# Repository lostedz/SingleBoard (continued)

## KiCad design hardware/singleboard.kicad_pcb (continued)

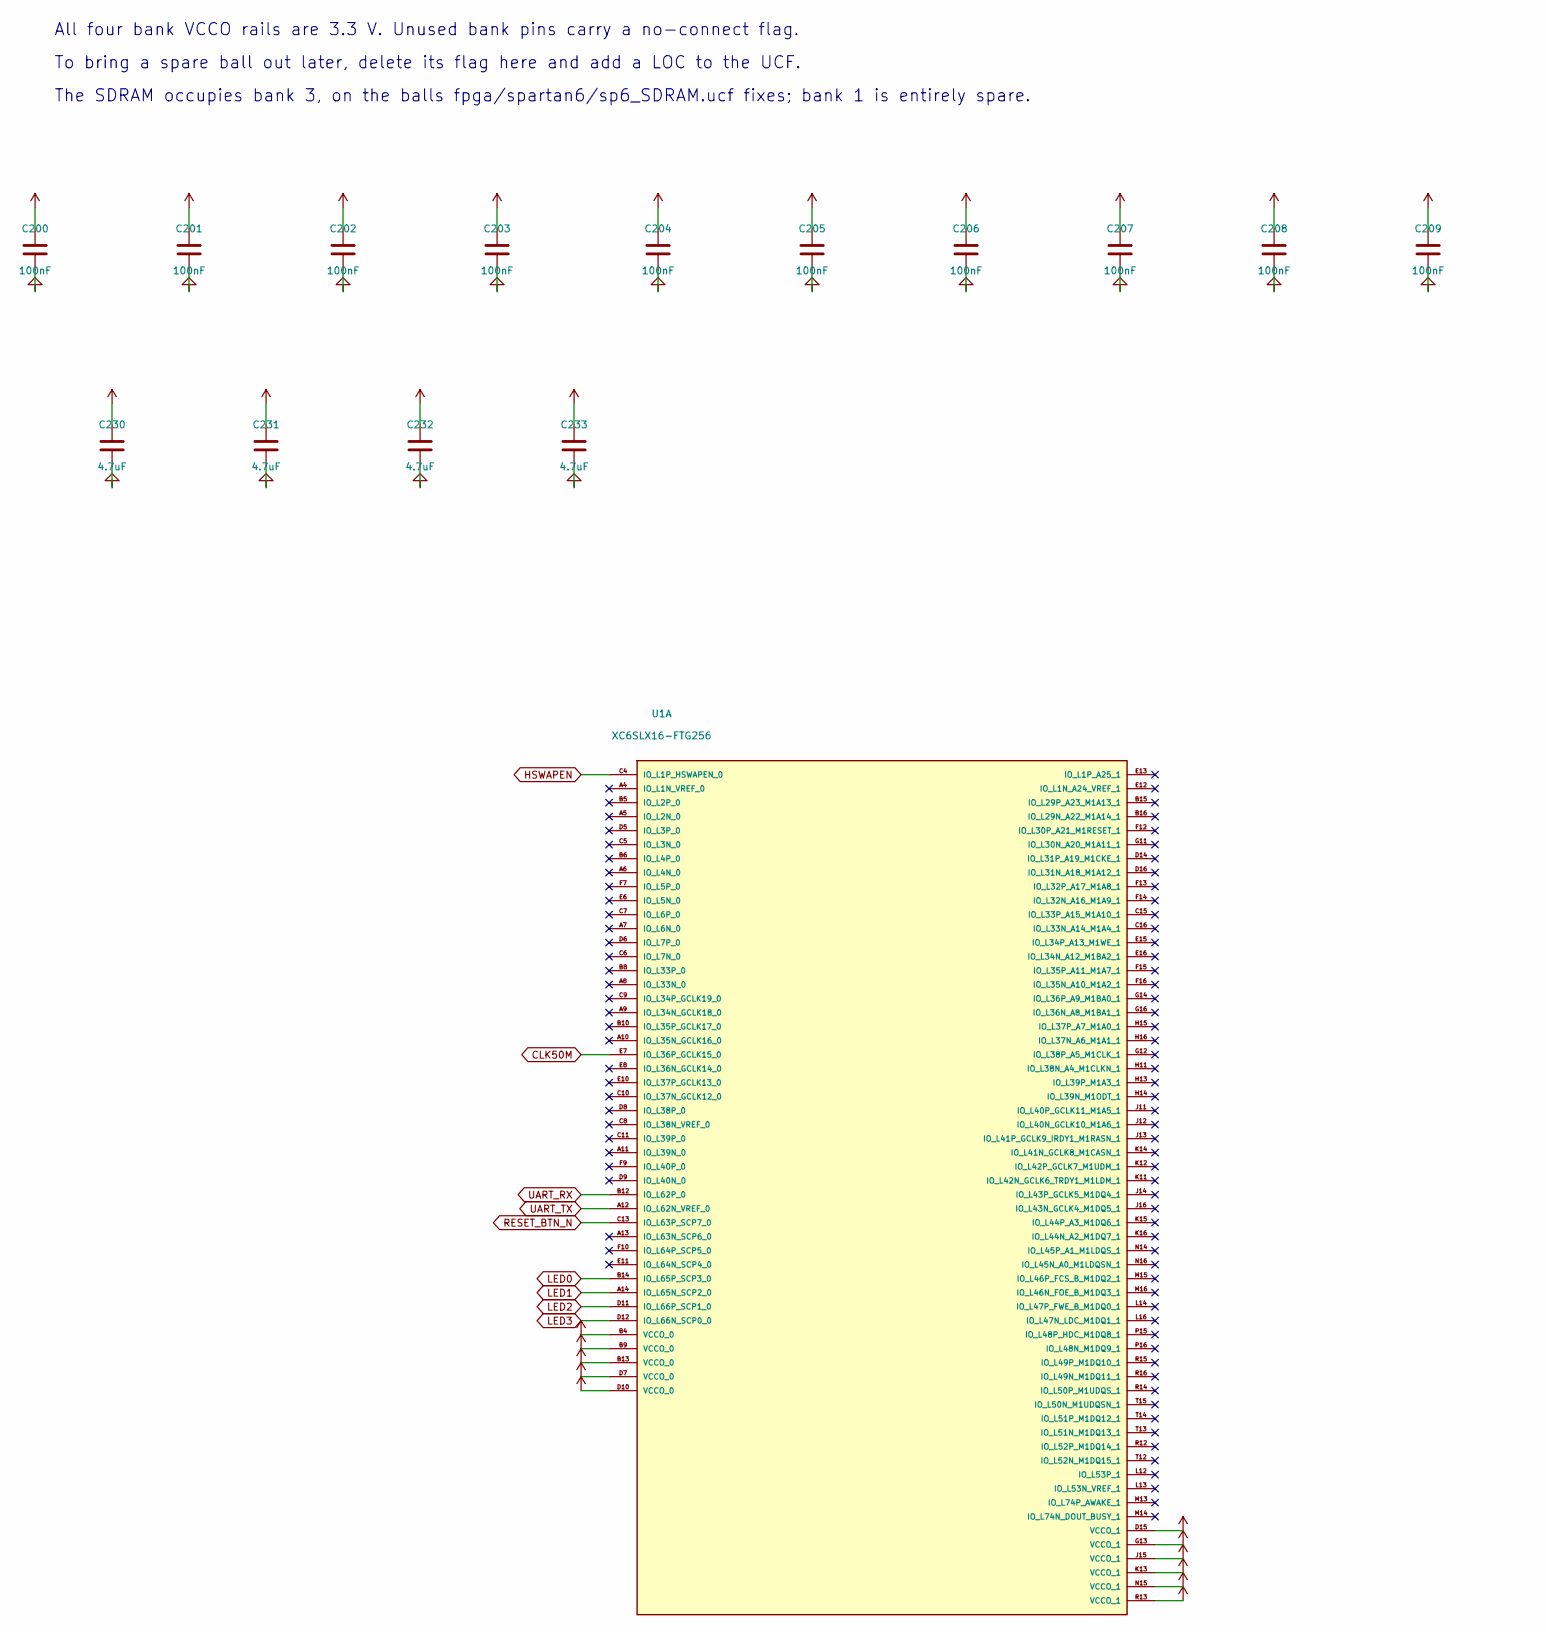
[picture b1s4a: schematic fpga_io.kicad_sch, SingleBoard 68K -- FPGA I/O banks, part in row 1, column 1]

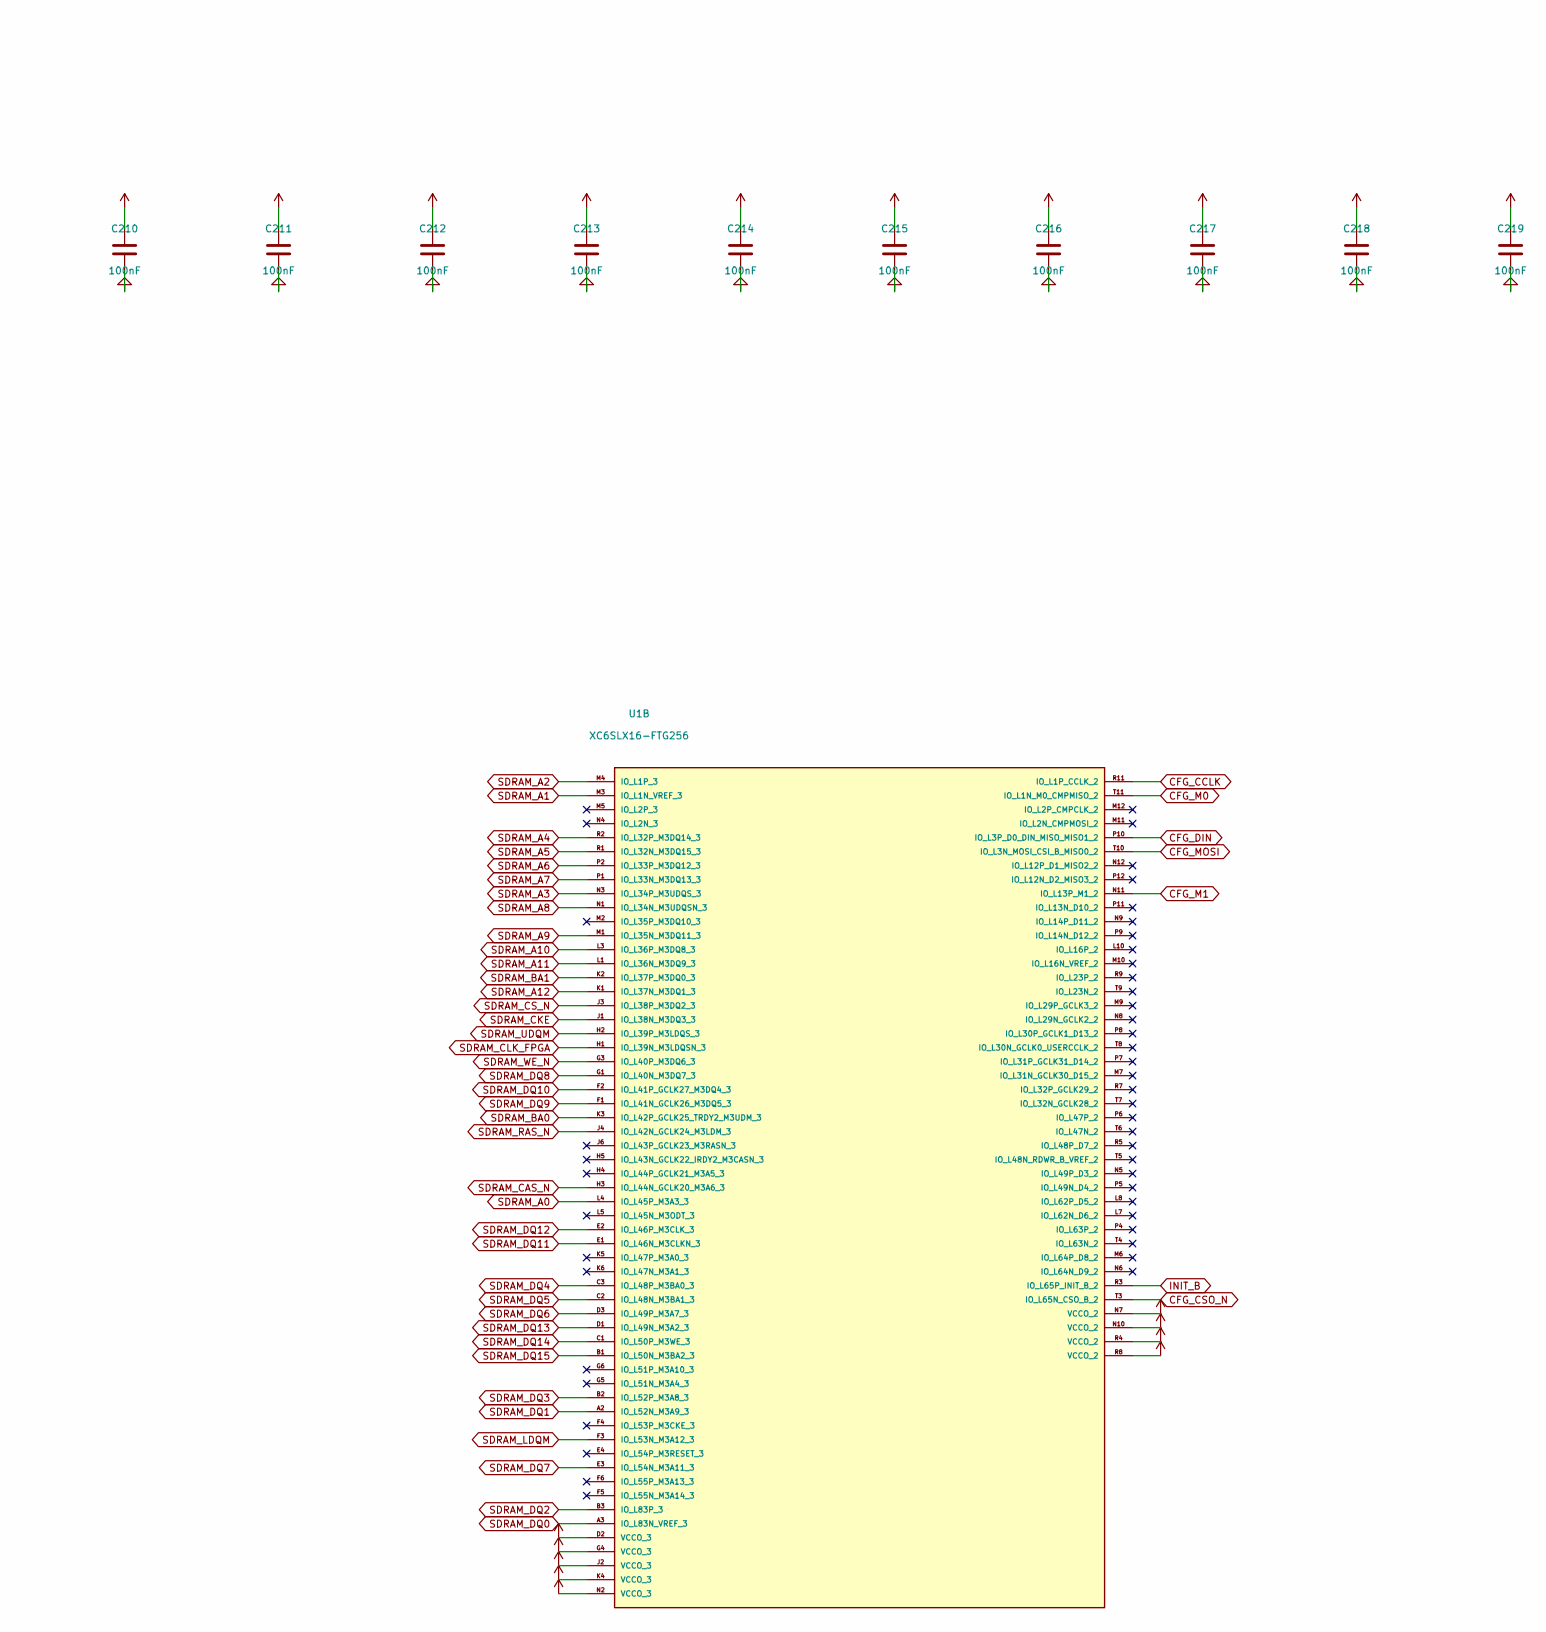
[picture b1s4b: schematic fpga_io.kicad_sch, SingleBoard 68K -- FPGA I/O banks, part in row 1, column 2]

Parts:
C200, C201, C202, C203, C204, C205, C206, C207, C208, C209, C210, C211, C212, C213, C214, C215, C216, C217, C218, C219: 100nF; C_0402_1005Metric
C230, C231, C232, C233: 4.7uF; C_0805_2012Metric
U1: XC6SLX16-FTG256; Xilinx_FTG256

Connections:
+3V3: C200.1, C201.1, C202.1, C203.1, C204.1, C205.1, C206.1, C207.1, C208.1, C209.1, C210.1, C211.1, C212.1, C213.1, C214.1, C215.1, C216.1, C217.1, C218.1, C219.1, C230.1, C231.1, C232.1, C233.1, U1.B4 (VCCO_0), U1.B9 (VCCO_0), U1.B13 (VCCO_0), U1.D2 (VCCO_3), U1.D7 (VCCO_0), U1.D10 (VCCO_0), U1.D15 (VCCO_1), U1.G4 (VCCO_3), U1.G13 (VCCO_1), U1.J2 (VCCO_3), U1.J15 (VCCO_1), U1.K4 (VCCO_3), U1.K13 (VCCO_1), U1.N2 (VCCO_3), U1.N7 (VCCO_2), U1.N10 (VCCO_2), U1.N15 (VCCO_1), U1.R4 (VCCO_2), U1.R8 (VCCO_2), U1.R13 (VCCO_1); also elsewhere on the board
CFG_CCLK: U1.R11 (IO_L1P_CCLK_2); also elsewhere on the board
CFG_CSO_N: U1.T3 (IO_L65N_CSO_B_2); also elsewhere on the board
CFG_DIN: U1.P10 (IO_L3P_D0_DIN_MISO_MISO1_2); also elsewhere on the board
CFG_M0: U1.T11 (IO_L1N_M0_CMPMISO_2); also elsewhere on the board
CFG_M1: U1.N11 (IO_L13P_M1_2); also elsewhere on the board
CFG_MOSI: U1.T10 (IO_L3N_MOSI_CSI_B_MISO0_2); also elsewhere on the board
CLK50M: U1.E7 (IO_L36P_GCLK15_0); also elsewhere on the board
GND: C200.2, C201.2, C202.2, C203.2, C204.2, C205.2, C206.2, C207.2, C208.2, C209.2, C210.2, C211.2, C212.2, C213.2, C214.2, C215.2, C216.2, C217.2, C218.2, C219.2, C230.2, C231.2, C232.2, C233.2; also elsewhere on the board
HSWAPEN: U1.C4 (IO_L1P_HSWAPEN_0); also elsewhere on the board
INIT_B: U1.R3 (IO_L65P_INIT_B_2); also elsewhere on the board
LED0: U1.B14 (IO_L65P_SCP3_0); also elsewhere on the board
LED1: U1.A14 (IO_L65N_SCP2_0); also elsewhere on the board
LED2: U1.D11 (IO_L66P_SCP1_0); also elsewhere on the board
LED3: U1.D12 (IO_L66N_SCP0_0); also elsewhere on the board
RESET_BTN_N: U1.C13 (IO_L63P_SCP7_0); also elsewhere on the board
SDRAM_A0: U1.L4 (IO_L45P_M3A3_3); also elsewhere on the board
SDRAM_A1: U1.M3 (IO_L1N_VREF_3); also elsewhere on the board
SDRAM_A2: U1.M4 (IO_L1P_3); also elsewhere on the board
SDRAM_A3: U1.N3 (IO_L34P_M3UDQS_3); also elsewhere on the board
SDRAM_A4: U1.R2 (IO_L32P_M3DQ14_3); also elsewhere on the board
SDRAM_A5: U1.R1 (IO_L32N_M3DQ15_3); also elsewhere on the board
SDRAM_A6: U1.P2 (IO_L33P_M3DQ12_3); also elsewhere on the board
SDRAM_A7: U1.P1 (IO_L33N_M3DQ13_3); also elsewhere on the board
SDRAM_A8: U1.N1 (IO_L34N_M3UDQSN_3); also elsewhere on the board
SDRAM_A9: U1.M1 (IO_L35N_M3DQ11_3); also elsewhere on the board
SDRAM_A10: U1.L3 (IO_L36P_M3DQ8_3); also elsewhere on the board
SDRAM_A11: U1.L1 (IO_L36N_M3DQ9_3); also elsewhere on the board
SDRAM_A12: U1.K1 (IO_L37N_M3DQ1_3); also elsewhere on the board
SDRAM_BA0: U1.K3 (IO_L42P_GCLK25_TRDY2_M3UDM_3); also elsewhere on the board
SDRAM_BA1: U1.K2 (IO_L37P_M3DQ0_3); also elsewhere on the board
SDRAM_CAS_N: U1.H3 (IO_L44N_GCLK20_M3A6_3); also elsewhere on the board
SDRAM_CKE: U1.J1 (IO_L38N_M3DQ3_3); also elsewhere on the board
SDRAM_CLK_FPGA: U1.H1 (IO_L39N_M3LDQSN_3); also elsewhere on the board
SDRAM_CS_N: U1.J3 (IO_L38P_M3DQ2_3); also elsewhere on the board
SDRAM_DQ0: U1.A3 (IO_L83N_VREF_3); also elsewhere on the board
SDRAM_DQ1: U1.A2 (IO_L52N_M3A9_3); also elsewhere on the board
SDRAM_DQ2: U1.B3 (IO_L83P_3); also elsewhere on the board
SDRAM_DQ3: U1.B2 (IO_L52P_M3A8_3); also elsewhere on the board
SDRAM_DQ4: U1.C3 (IO_L48P_M3BA0_3); also elsewhere on the board
SDRAM_DQ5: U1.C2 (IO_L48N_M3BA1_3); also elsewhere on the board
SDRAM_DQ6: U1.D3 (IO_L49P_M3A7_3); also elsewhere on the board
SDRAM_DQ7: U1.E3 (IO_L54N_M3A11_3); also elsewhere on the board
SDRAM_DQ8: U1.G1 (IO_L40N_M3DQ7_3); also elsewhere on the board
SDRAM_DQ9: U1.F1 (IO_L41N_GCLK26_M3DQ5_3); also elsewhere on the board
SDRAM_DQ10: U1.F2 (IO_L41P_GCLK27_M3DQ4_3); also elsewhere on the board
SDRAM_DQ11: U1.E1 (IO_L46N_M3CLKN_3); also elsewhere on the board
SDRAM_DQ12: U1.E2 (IO_L46P_M3CLK_3); also elsewhere on the board
SDRAM_DQ13: U1.D1 (IO_L49N_M3A2_3); also elsewhere on the board
SDRAM_DQ14: U1.C1 (IO_L50P_M3WE_3); also elsewhere on the board
SDRAM_DQ15: U1.B1 (IO_L50N_M3BA2_3); also elsewhere on the board
SDRAM_LDQM: U1.F3 (IO_L53N_M3A12_3); also elsewhere on the board
SDRAM_RAS_N: U1.J4 (IO_L42N_GCLK24_M3LDM_3); also elsewhere on the board
SDRAM_UDQM: U1.H2 (IO_L39P_M3LDQS_3); also elsewhere on the board
SDRAM_WE_N: U1.G3 (IO_L40P_M3DQ6_3); also elsewhere on the board
UART_RX: U1.B12 (IO_L62P_0); also elsewhere on the board
UART_TX: U1.A12 (IO_L62N_VREF_0); also elsewhere on the board

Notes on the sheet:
All four bank VCCO rails are 3.3 V. Unused bank pins carry a no-connect flag.
To bring a spare ball out later, delete its flag here and add a LOC to the UCF.
The SDRAM occupies bank 3, on the balls fpga/spartan6/sp6_SDRAM.ucf fixes; bank 1 is entirely spare.

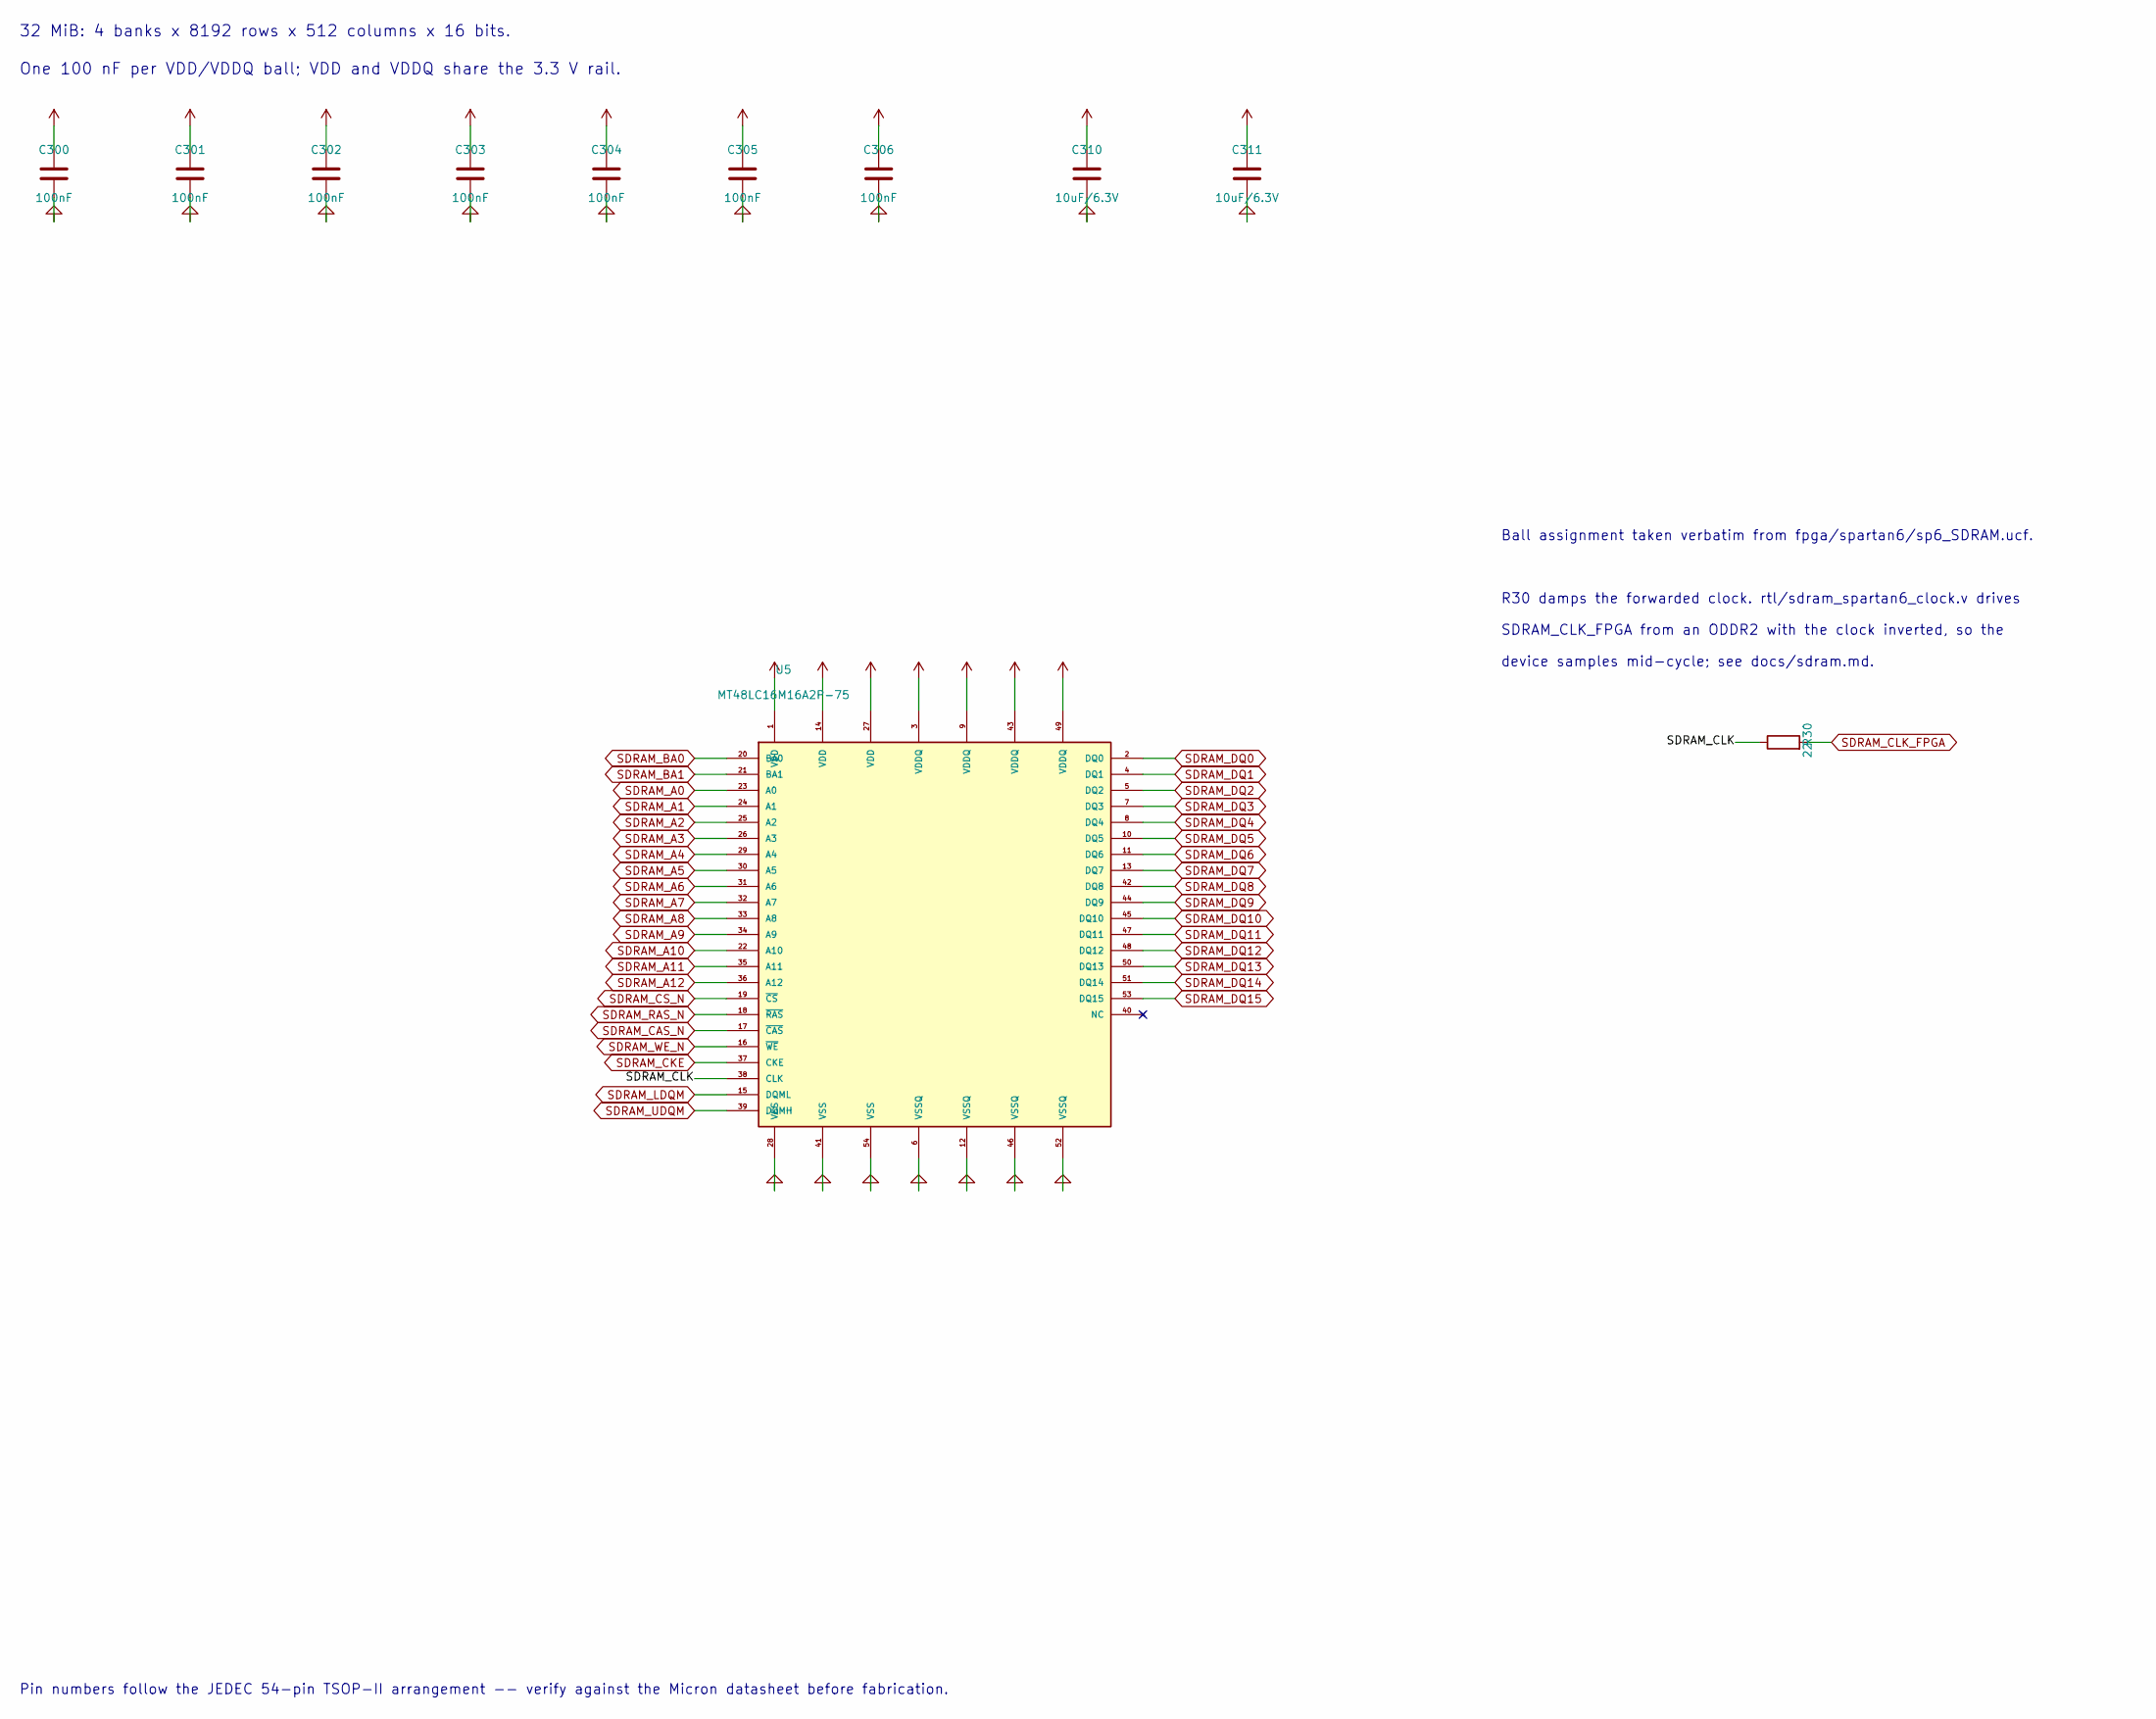
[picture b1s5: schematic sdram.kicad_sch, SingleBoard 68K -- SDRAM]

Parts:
C300, C301, C302, C303, C304, C305, C306: 100nF; C_0402_1005Metric
C310, C311: 10uF/6.3V; C_0805_2012Metric
R30: 22; R_0402_1005Metric
U5: MT48LC16M16A2P-75; TSOP-II-54_22.2x10.16mm_P0.8mm

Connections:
+3V3: C300.1, C301.1, C302.1, C303.1, C304.1, C305.1, C306.1, C310.1, C311.1, U5.1 (VDD), U5.3 (VDDQ), U5.9 (VDDQ), U5.14 (VDD), U5.27 (VDD), U5.43 (VDDQ), U5.49 (VDDQ); also elsewhere on the board
/sdram/SDRAM_CLK: R30.1, U5.38 (CLK)
GND: C300.2, C301.2, C302.2, C303.2, C304.2, C305.2, C306.2, C310.2, C311.2, U5.6 (VSSQ), U5.12 (VSSQ), U5.28 (VSS), U5.41 (VSS), U5.46 (VSSQ), U5.52 (VSSQ), U5.54 (VSS); also elsewhere on the board
SDRAM_A0: U5.23 (A0); also elsewhere on the board
SDRAM_A1: U5.24 (A1); also elsewhere on the board
SDRAM_A2: U5.25 (A2); also elsewhere on the board
SDRAM_A3: U5.26 (A3); also elsewhere on the board
SDRAM_A4: U5.29 (A4); also elsewhere on the board
SDRAM_A5: U5.30 (A5); also elsewhere on the board
SDRAM_A6: U5.31 (A6); also elsewhere on the board
SDRAM_A7: U5.32 (A7); also elsewhere on the board
SDRAM_A8: U5.33 (A8); also elsewhere on the board
SDRAM_A9: U5.34 (A9); also elsewhere on the board
SDRAM_A10: U5.22 (A10); also elsewhere on the board
SDRAM_A11: U5.35 (A11); also elsewhere on the board
SDRAM_A12: U5.36 (A12); also elsewhere on the board
SDRAM_BA0: U5.20 (BA0); also elsewhere on the board
SDRAM_BA1: U5.21 (BA1); also elsewhere on the board
SDRAM_CAS_N: U5.17 (~CAS); also elsewhere on the board
SDRAM_CKE: U5.37 (CKE); also elsewhere on the board
SDRAM_CLK_FPGA: R30.2; also elsewhere on the board
SDRAM_CS_N: U5.19 (~CS); also elsewhere on the board
SDRAM_DQ0: U5.2 (DQ0); also elsewhere on the board
SDRAM_DQ1: U5.4 (DQ1); also elsewhere on the board
SDRAM_DQ2: U5.5 (DQ2); also elsewhere on the board
SDRAM_DQ3: U5.7 (DQ3); also elsewhere on the board
SDRAM_DQ4: U5.8 (DQ4); also elsewhere on the board
SDRAM_DQ5: U5.10 (DQ5); also elsewhere on the board
SDRAM_DQ6: U5.11 (DQ6); also elsewhere on the board
SDRAM_DQ7: U5.13 (DQ7); also elsewhere on the board
SDRAM_DQ8: U5.42 (DQ8); also elsewhere on the board
SDRAM_DQ9: U5.44 (DQ9); also elsewhere on the board
SDRAM_DQ10: U5.45 (DQ10); also elsewhere on the board
SDRAM_DQ11: U5.47 (DQ11); also elsewhere on the board
SDRAM_DQ12: U5.48 (DQ12); also elsewhere on the board
SDRAM_DQ13: U5.50 (DQ13); also elsewhere on the board
SDRAM_DQ14: U5.51 (DQ14); also elsewhere on the board
SDRAM_DQ15: U5.53 (DQ15); also elsewhere on the board
SDRAM_LDQM: U5.15 (DQML); also elsewhere on the board
SDRAM_RAS_N: U5.18 (~RAS); also elsewhere on the board
SDRAM_UDQM: U5.39 (DQMH); also elsewhere on the board
SDRAM_WE_N: U5.16 (~WE); also elsewhere on the board

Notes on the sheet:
Ball assignment taken verbatim from fpga/spartan6/sp6_SDRAM.ucf.
R30 damps the forwarded clock. rtl/sdram_spartan6_clock.v drives
SDRAM_CLK_FPGA from an ODDR2 with the clock inverted, so the
device samples mid-cycle; see docs/sdram.md.
32 MiB: 4 banks x 8192 rows x 512 columns x 16 bits.
One 100 nF per VDD/VDDQ ball; VDD and VDDQ share the 3.3 V rail.
Pin numbers follow the JEDEC 54-pin TSOP-II arrangement -- verify against the Micron datasheet before fabrication.

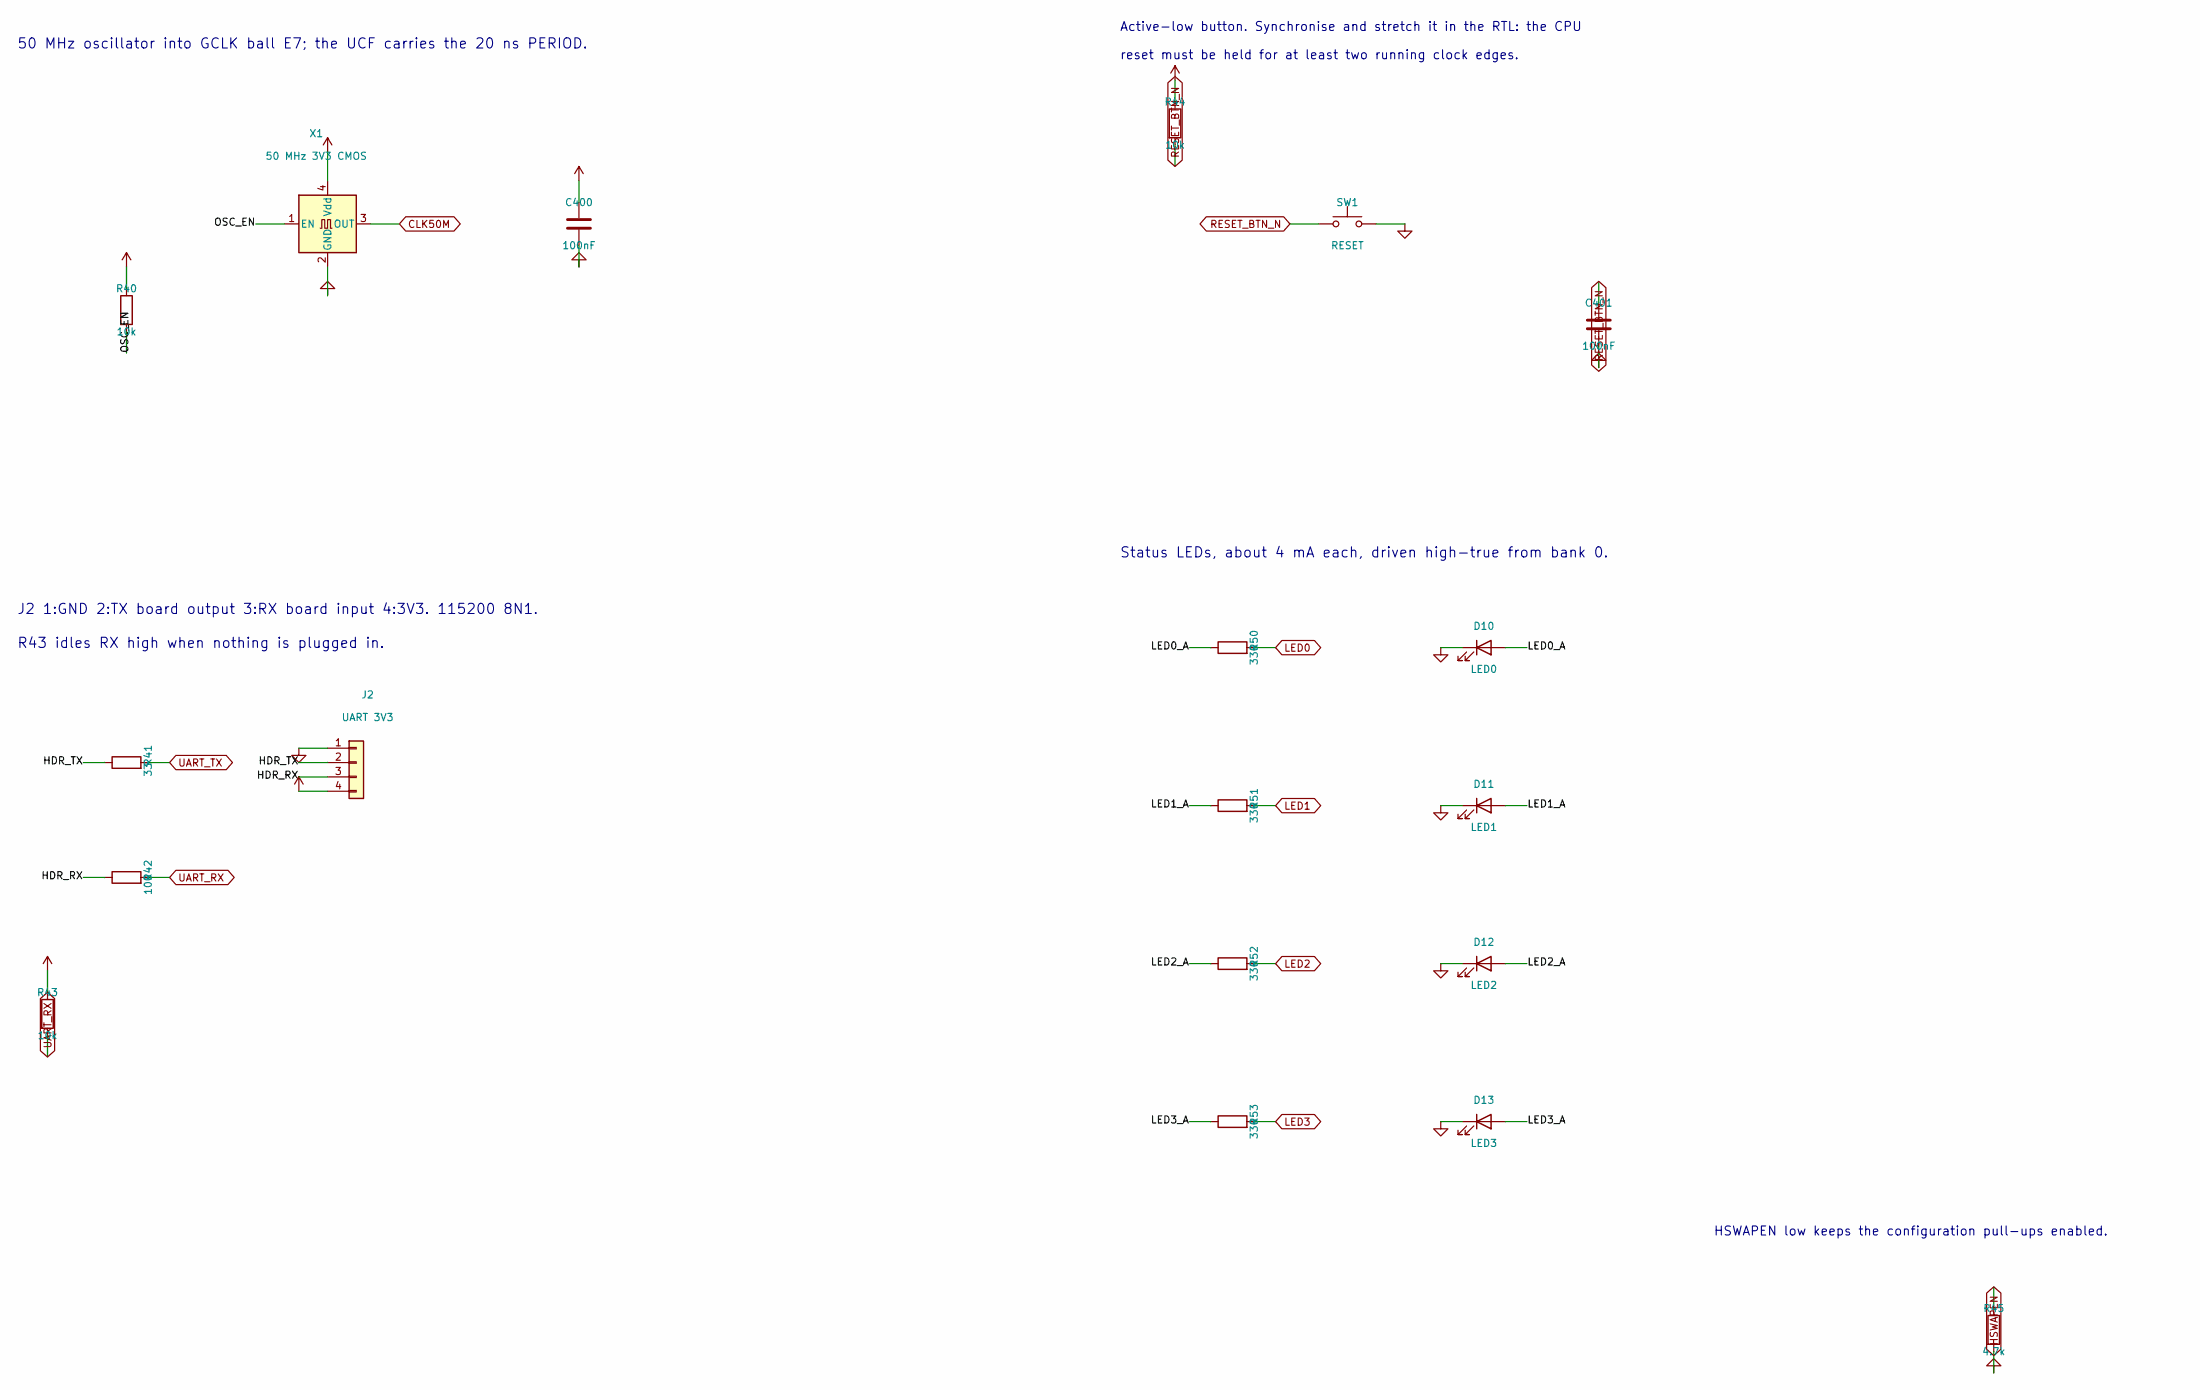
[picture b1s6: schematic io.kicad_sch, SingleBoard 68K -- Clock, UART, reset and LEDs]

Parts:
C400, C401: 100nF; C_0402_1005Metric
D10: LED0; LED_0603_1608Metric
D11: LED1; LED_0603_1608Metric
D12: LED2; LED_0603_1608Metric
D13: LED3; LED_0603_1608Metric
J2: UART 3V3; PinHeader_1x04_P2.54mm_Vertical
R40, R43, R44: 10k; R_0402_1005Metric
R41: 33; R_0402_1005Metric
R42: 100; R_0402_1005Metric
R45: 4.7k; R_0402_1005Metric
R50, R51, R52, R53: 330; R_0402_1005Metric
SW1: RESET; SW_SPST_SKQG_WithStem
X1: 50 MHz 3V3 CMOS; Oscillator_SMD_Abracon_ASE-4Pin_3.2x2.5mm

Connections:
+3V3: C400.1, J2.4, R40.1, R43.1, R44.1, X1.4 (Vdd); also elsewhere on the board
/io/HDR_RX: J2.3, R42.1
/io/HDR_TX: J2.2, R41.1
/io/LED0_A: D10.2 (A), R50.1
/io/LED1_A: D11.2 (A), R51.1
/io/LED2_A: D12.2 (A), R52.1
/io/LED3_A: D13.2 (A), R53.1
/io/OSC_EN: R40.2, X1.1 (EN)
CLK50M: X1.3 (OUT); also elsewhere on the board
GND: C400.2, C401.2, D10.1 (K), D11.1 (K), D12.1 (K), D13.1 (K), J2.1, R45.2, SW1.2, X1.2 (GND); also elsewhere on the board
HSWAPEN: R45.1; also elsewhere on the board
LED0: R50.2; also elsewhere on the board
LED1: R51.2; also elsewhere on the board
LED2: R52.2; also elsewhere on the board
LED3: R53.2; also elsewhere on the board
RESET_BTN_N: C401.1, R44.2, SW1.1; also elsewhere on the board
UART_RX: R42.2, R43.2; also elsewhere on the board
UART_TX: R41.2; also elsewhere on the board

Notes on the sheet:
50 MHz oscillator into GCLK ball E7; the UCF carries the 20 ns PERIOD.
J2 1:GND 2:TX board output 3:RX board input 4:3V3. 115200 8N1.
R43 idles RX high when nothing is plugged in.
Active-low button. Synchronise and stretch it in the RTL: the CPU
reset must be held for at least two running clock edges.
Status LEDs, about 4 mA each, driven high-true from bank 0.
HSWAPEN low keeps the configuration pull-ups enabled.

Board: 4 copper layers, 129 parts (43 on the bottom side), 88 nets, no tracks yet.

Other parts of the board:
H1, H2, H3, H4: M3; MountingHole_3.2mm_M3

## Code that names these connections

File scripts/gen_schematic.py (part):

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    tag(sh, "Connector:Barrel_Jack", 1, (30, 45), "VIN_RAW", kind="local")
    tag(sh, "Connector:Barrel_Jack", 2, (30, 45), "GND", kind="power")

    two_pin(sh, "Device:Polyfuse", "F1", "1.1A hold", (76, 42.46), "VIN_F", "VIN_RAW",
            rot=90, footprint=FP["fuse"], stub=7.62)
    two_pin(sh, "Device:D_Schottky", "D1", "SS34", (117, 42.46), "+5V", "VIN_F",
            rot=180, footprint=FP["diode"], a_kind="power", stub=7.62)
    two_pin(sh, "Device:D_TVS", "D2", "SMAJ5.0A", (145, 55), "+5V", "GND",
            rot=90, footprint=FP["diode"], a_kind="power", b_kind="power")
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    # Enable network: VCCINT (1V2) is released first, VCCO/VCCAUX (3V3) after
    # an RC delay. Spartan-6 does not require a sequence; this follows the
    # recommended VCCINT-before-VCCO order.
    two_pin(sh, "Device:R", "R3", "100k", (150, 100), "+5V", "EN_3V3",
            footprint=FP["r"], a_kind="power")
    two_pin(sh, "Device:C", "C3", "1uF", (150, 124), "EN_3V3", "GND",
            footprint=FP["c"], b_kind="power")
    two_pin(sh, "Device:R", "R7", "100k", (150, 200), "+5V", "EN_1V2",
            footprint=FP["r"], a_kind="power")
    sh.text("R3/C3 delay the 3V3 enable ~100 ms behind 1V2.", (95, 140), 1.6)

    # Power indicator and test points.
    two_pin(sh, "Device:R", "R4", "1k", (30, 240), "+3V3", "PWR_LED",
            footprint=FP["r"], a_kind="power")
    two_pin(sh, "Device:LED", "D3", "PWR green", (58, 262), "GND", "PWR_LED",
            footprint=FP["led"], a_kind="power")
    for i, (rail, x) in enumerate([("+5V", 110), ("+3V3", 135), ("+1V2", 160),
                                   ("GND", 185)]):
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            tag(sh, FPGA, p["ball"], cat, net, kind="global")

    # Configuration straps.
    two_pin(sh, "Device:R", "R10", "4.7k", (330, 120), "+3V3", "PROGRAM_B",
            footprint=FP["r"], a_kind="power", b_kind="global")
    sh.symbol("Switch:SW_Push", "SW2", "PROG", (340, 145), footprint=FP["sw"])
    tag(sh, "Switch:SW_Push", 1, (340, 145), "PROGRAM_B", kind="global")
    tag(sh, "Switch:SW_Push", 2, (340, 145), "GND", kind="power")
    two_pin(sh, "Device:R", "R11", "4.7k", (365, 120), "+3V3", "INIT_B",
            footprint=FP["r"], a_kind="power", b_kind="global")
    two_pin(sh, "Device:R", "R12", "4.7k", (398, 120), "+3V3", "CMPCS_B",
            footprint=FP["r"], a_kind="power", b_kind="global")

    # DONE: 330 ohm pull-up per UG380 plus an LED lit while unconfigured.
    two_pin(sh, "Device:R", "R13", "330", (330, 180), "+3V3", "DONE",
            footprint=FP["r"], a_kind="power", b_kind="global")
    two_pin(sh, "Device:R", "R14", "1k", (365, 180), "+3V3", "DONE_LED",
            footprint=FP["r"], a_kind="power")
    two_pin(sh, "Device:LED", "D4", "nDONE red", (395, 192), "DONE", "DONE_LED",
            footprint=FP["led"], a_kind="global")

    # Mode pins: M[1:0] = 01 selects master SPI on Spartan-6. Each strap has a
    # fitted resistor and a DNP alternate so the mode can be changed by rework.
    two_pin(sh, "Device:R", "R15", "4.7k", (330, 230), "+3V3", "CFG_M0",
            footprint=FP["r"], a_kind="power", b_kind="global")
    two_pin(sh, "Device:R", "R16", "4.7k", (352, 230), "CFG_M0", "GND",
            footprint=FP["r"], a_kind="global", b_kind="power", dnp=True)
    two_pin(sh, "Device:R", "R17", "4.7k", (378, 230), "+3V3", "CFG_M1",
            footprint=FP["r"], a_kind="power", b_kind="global", dnp=True)
    two_pin(sh, "Device:R", "R18", "4.7k", (400, 230), "CFG_M1", "GND",
            footprint=FP["r"], a_kind="global", b_kind="power")
    sh.text("M[1:0] = 01 selects master SPI. R16/R17 are DNP alternates;", (320, 258), 1.4)
    sh.text("confirm the encoding against UG380 Table 2-3 before build.", (320, 262), 1.4)
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    tag(sh, "Memory_Flash:W25Q32JVSS", 7, fat, "FLASH_HOLD_N", kind="local")
    tag(sh, "Memory_Flash:W25Q32JVSS", 8, fat, "+3V3", kind="power")
    tag(sh, "Memory_Flash:W25Q32JVSS", 4, fat, "GND", kind="power")
    two_pin(sh, "Device:R", "R19", "10k", (135, 235), "+3V3", "FLASH_WP_N",
            footprint=FP["r"], a_kind="power")
    two_pin(sh, "Device:R", "R20", "10k", (160, 235), "+3V3", "FLASH_HOLD_N",
            footprint=FP["r"], a_kind="power")
    decap(sh, "C150", "100nF", (135, 265), "+3V3", footprint=FP["c"])
    sh.text("32 Mbit boot flash; an XC6SLX16 bitstream is about 3.73 Mbit.", (20, 215), 1.6)
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        tag(sh, SDRAM, num, at, "GND", kind="power")
    tag(sh, SDRAM, "40", at, "", kind="nc")

    two_pin(sh, "Device:R", "R30", "22", (310, 135), "SDRAM_CLK_FPGA", "SDRAM_CLK",
            rot=90, footprint=FP["r"], a_kind="global", b_kind="local")
    sh.text("Ball assignment taken verbatim from fpga/spartan6/sp6_SDRAM.ucf.", (265, 102), 1.6)
    sh.text("R30 damps the forwarded clock. rtl/sdram_spartan6_clock.v drives", (265, 112), 1.6)
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    tag(sh, "Oscillator:ASE-xxxMHz", 2, oat, "GND", kind="power")
    tag(sh, "Oscillator:ASE-xxxMHz", 3, oat, "CLK50M", kind="global")
    tag(sh, "Oscillator:ASE-xxxMHz", 1, oat, "OSC_EN", kind="local")
    two_pin(sh, "Device:R", "R40", "10k", (40, 75), "+3V3", "OSC_EN",
            footprint=FP["r"], a_kind="power")
    decap(sh, "C400", "100nF", (120, 60), "+3V3", footprint=FP["c"])
    sh.text("50 MHz oscillator into GCLK ball E7; the UCF carries the 20 ns "
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    tag(sh, "Connector_Generic:Conn_01x04", 2, uat, "HDR_TX", kind="local")
    tag(sh, "Connector_Generic:Conn_01x04", 3, uat, "HDR_RX", kind="local")
    tag(sh, "Connector_Generic:Conn_01x04", 4, uat, "+3V3", kind="power")
    two_pin(sh, "Device:R", "R41", "33", (40, 155), "UART_TX", "HDR_TX",
            rot=90, footprint=FP["r"], a_kind="global")
    two_pin(sh, "Device:R", "R42", "100", (40, 175), "UART_RX", "HDR_RX",
            rot=90, footprint=FP["r"], a_kind="global")
    two_pin(sh, "Device:R", "R43", "10k", (25, 200), "+3V3", "UART_RX",
            footprint=FP["r"], a_kind="power", b_kind="global")
    sh.text("J2 1:GND 2:TX board output 3:RX board input 4:3V3. 115200 8N1.", (20, 128), 1.8)
    sh.text("R43 idles RX high when nothing is plugged in.", (20, 134), 1.8)
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    sh.symbol("Switch:SW_Push", "SW1", "RESET", rat, footprint=FP["sw"])
    tag(sh, "Switch:SW_Push", 1, rat, "RESET_BTN_N", kind="global")
    tag(sh, "Switch:SW_Push", 2, rat, "GND", kind="power")
    two_pin(sh, "Device:R", "R44", "10k", (225, 42), "+3V3", "RESET_BTN_N",
            footprint=FP["r"], a_kind="power", b_kind="global")
    two_pin(sh, "Device:C", "C401", "100nF", (300, 78), "RESET_BTN_N", "GND",
            footprint=FP["c"], a_kind="global", b_kind="power")
    sh.text("Active-low button. Synchronise and stretch it in the RTL: the CPU", (215, 25), 1.6)
    sh.text("reset must be held for at least two running clock edges.", (215, 30), 1.6)
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    sh.text("Status LEDs, about 4 mA each, driven high-true from bank 0.", (215, 118), 1.8)

    # HSWAPEN: pulled low so the internal pull-ups stay active during config.
    two_pin(sh, "Device:R", "R45", "4.7k", (370, 255), "HSWAPEN", "GND",
            footprint=FP["r"], a_kind="global", b_kind="power")
    sh.text("HSWAPEN low keeps the configuration pull-ups enabled.", (320, 238), 1.6)

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                 % (width, '"%s"' % port, IO_MAP[net]))
    L += ["",
          "# Dedicated configuration pins are fixed by the device and need no",
          "# LOC: TCK C14, TDI C12, TDO E14, TMS A15, DONE P13, PROGRAM_B T2,",
          "# SUSPEND P14, CMPCS_B L11.",
          "# Master-SPI configuration uses CCLK R11, MOSI T10, DIN P10,",
          "# CSO_B T3 and INIT_B R3, with mode pins M0 T11 high and M1 N11 low.",
          "# HSWAPEN C4 is strapped low on the board.",
          ""]
    path = os.path.join(ROOT, "fpga", "spartan6", "singleboard.ucf")
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
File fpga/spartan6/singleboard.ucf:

# SingleBoard 68K board constraints for XC6SLX16-FTG256.
#
# Generated by scripts/gen_schematic.py from the same ball assignment
# as hardware/singleboard.kicad_sch. Do not edit by hand: change the
# tables in that script and re-run it.
#
# The SDRAM LOCs are read from sp6_SDRAM.ucf, the reference Spartan-6
# SDRAM board's constraints, so the schematic follows that board.
# Only the signal names are translated; no ball was chosen here.
#
# Port names follow rtl/sdram_mt48lc16m16a2.v, rtl/uart_mmio.v and
# rtl/sdram_spartan6_clock.v. Rename the left-hand side if the
# board-level top module uses different port names.
#
# No ISE run has validated this file. Nothing here has been placed,
# routed or timed.

CONFIG VCCAUX = 3.3;

NET "clk50m" TNM_NET = "clk50m";
TIMESPEC TS_clk50m = PERIOD "clk50m" 20.0 ns HIGH 50%;

NET "clk50m"          LOC = E7   | IOSTANDARD = LVCMOS33;
NET "uart_rx"         LOC = B12  | IOSTANDARD = LVCMOS33;
NET "uart_tx"         LOC = A12  | IOSTANDARD = LVCMOS33;
NET "reset_btn_n"     LOC = C13  | IOSTANDARD = LVCMOS33;

NET "led<0>"          LOC = B14  | IOSTANDARD = LVCMOS33;
NET "led<1>"          LOC = A14  | IOSTANDARD = LVCMOS33;
NET "led<2>"          LOC = D11  | IOSTANDARD = LVCMOS33;
NET "led<3>"          LOC = D12  | IOSTANDARD = LVCMOS33;

NET "sdram_addr<0>"   LOC = L4   | IOSTANDARD = LVCMOS33;
NET "sdram_addr<1>"   LOC = M3   | IOSTANDARD = LVCMOS33;
NET "sdram_addr<2>"   LOC = M4   | IOSTANDARD = LVCMOS33;
NET "sdram_addr<3>"   LOC = N3   | IOSTANDARD = LVCMOS33;
NET "sdram_addr<4>"   LOC = R2   | IOSTANDARD = LVCMOS33;
NET "sdram_addr<5>"   LOC = R1   | IOSTANDARD = LVCMOS33;
NET "sdram_addr<6>"   LOC = P2   | IOSTANDARD = LVCMOS33;
NET "sdram_addr<7>"   LOC = P1   | IOSTANDARD = LVCMOS33;
NET "sdram_addr<8>"   LOC = N1   | IOSTANDARD = LVCMOS33;
NET "sdram_addr<9>"   LOC = M1   | IOSTANDARD = LVCMOS33;
NET "sdram_addr<10>"  LOC = L3   | IOSTANDARD = LVCMOS33;
NET "sdram_addr<11>"  LOC = L1   | IOSTANDARD = LVCMOS33;
NET "sdram_addr<12>"  LOC = K1   | IOSTANDARD = LVCMOS33;

NET "sdram_ba<0>"     LOC = K3   | IOSTANDARD = LVCMOS33;
NET "sdram_ba<1>"     LOC = K2   | IOSTANDARD = LVCMOS33;

NET "sdram_dq<0>"     LOC = A3   | IOSTANDARD = LVCMOS33;
NET "sdram_dq<1>"     LOC = A2   | IOSTANDARD = LVCMOS33;
NET "sdram_dq<2>"     LOC = B3   | IOSTANDARD = LVCMOS33;
NET "sdram_dq<3>"     LOC = B2   | IOSTANDARD = LVCMOS33;
NET "sdram_dq<4>"     LOC = C3   | IOSTANDARD = LVCMOS33;
NET "sdram_dq<5>"     LOC = C2   | IOSTANDARD = LVCMOS33;
NET "sdram_dq<6>"     LOC = D3   | IOSTANDARD = LVCMOS33;
NET "sdram_dq<7>"     LOC = E3   | IOSTANDARD = LVCMOS33;
NET "sdram_dq<8>"     LOC = G1   | IOSTANDARD = LVCMOS33;
NET "sdram_dq<9>"     LOC = F1   | IOSTANDARD = LVCMOS33;
NET "sdram_dq<10>"    LOC = F2   | IOSTANDARD = LVCMOS33;
NET "sdram_dq<11>"    LOC = E1   | IOSTANDARD = LVCMOS33;
NET "sdram_dq<12>"    LOC = E2   | IOSTANDARD = LVCMOS33;
NET "sdram_dq<13>"    LOC = D1   | IOSTANDARD = LVCMOS33;
NET "sdram_dq<14>"    LOC = C1   | IOSTANDARD = LVCMOS33;
NET "sdram_dq<15>"    LOC = B1   | IOSTANDARD = LVCMOS33;

NET "sdram_dqm<0>"    LOC = F3   | IOSTANDARD = LVCMOS33;
NET "sdram_dqm<1>"    LOC = H2   | IOSTANDARD = LVCMOS33;

NET "sdram_cke"       LOC = J1   | IOSTANDARD = LVCMOS33;
NET "sdram_cs_n"      LOC = J3   | IOSTANDARD = LVCMOS33;
NET "sdram_ras_n"     LOC = J4   | IOSTANDARD = LVCMOS33;
NET "sdram_cas_n"     LOC = H3   | IOSTANDARD = LVCMOS33;
NET "sdram_we_n"      LOC = G3   | IOSTANDARD = LVCMOS33;
NET "sdram_clk"       LOC = H1   | IOSTANDARD = LVCMOS33;

# Dedicated configuration pins are fixed by the device and need no
# LOC: TCK C14, TDI C12, TDO E14, TMS A15, DONE P13, PROGRAM_B T2,
# SUSPEND P14, CMPCS_B L11.
# Master-SPI configuration uses CCLK R11, MOSI T10, DIN P10,
# CSO_B T3 and INIT_B R3, with mode pins M0 T11 high and M1 N11 low.
# HSWAPEN C4 is strapped low on the board.
